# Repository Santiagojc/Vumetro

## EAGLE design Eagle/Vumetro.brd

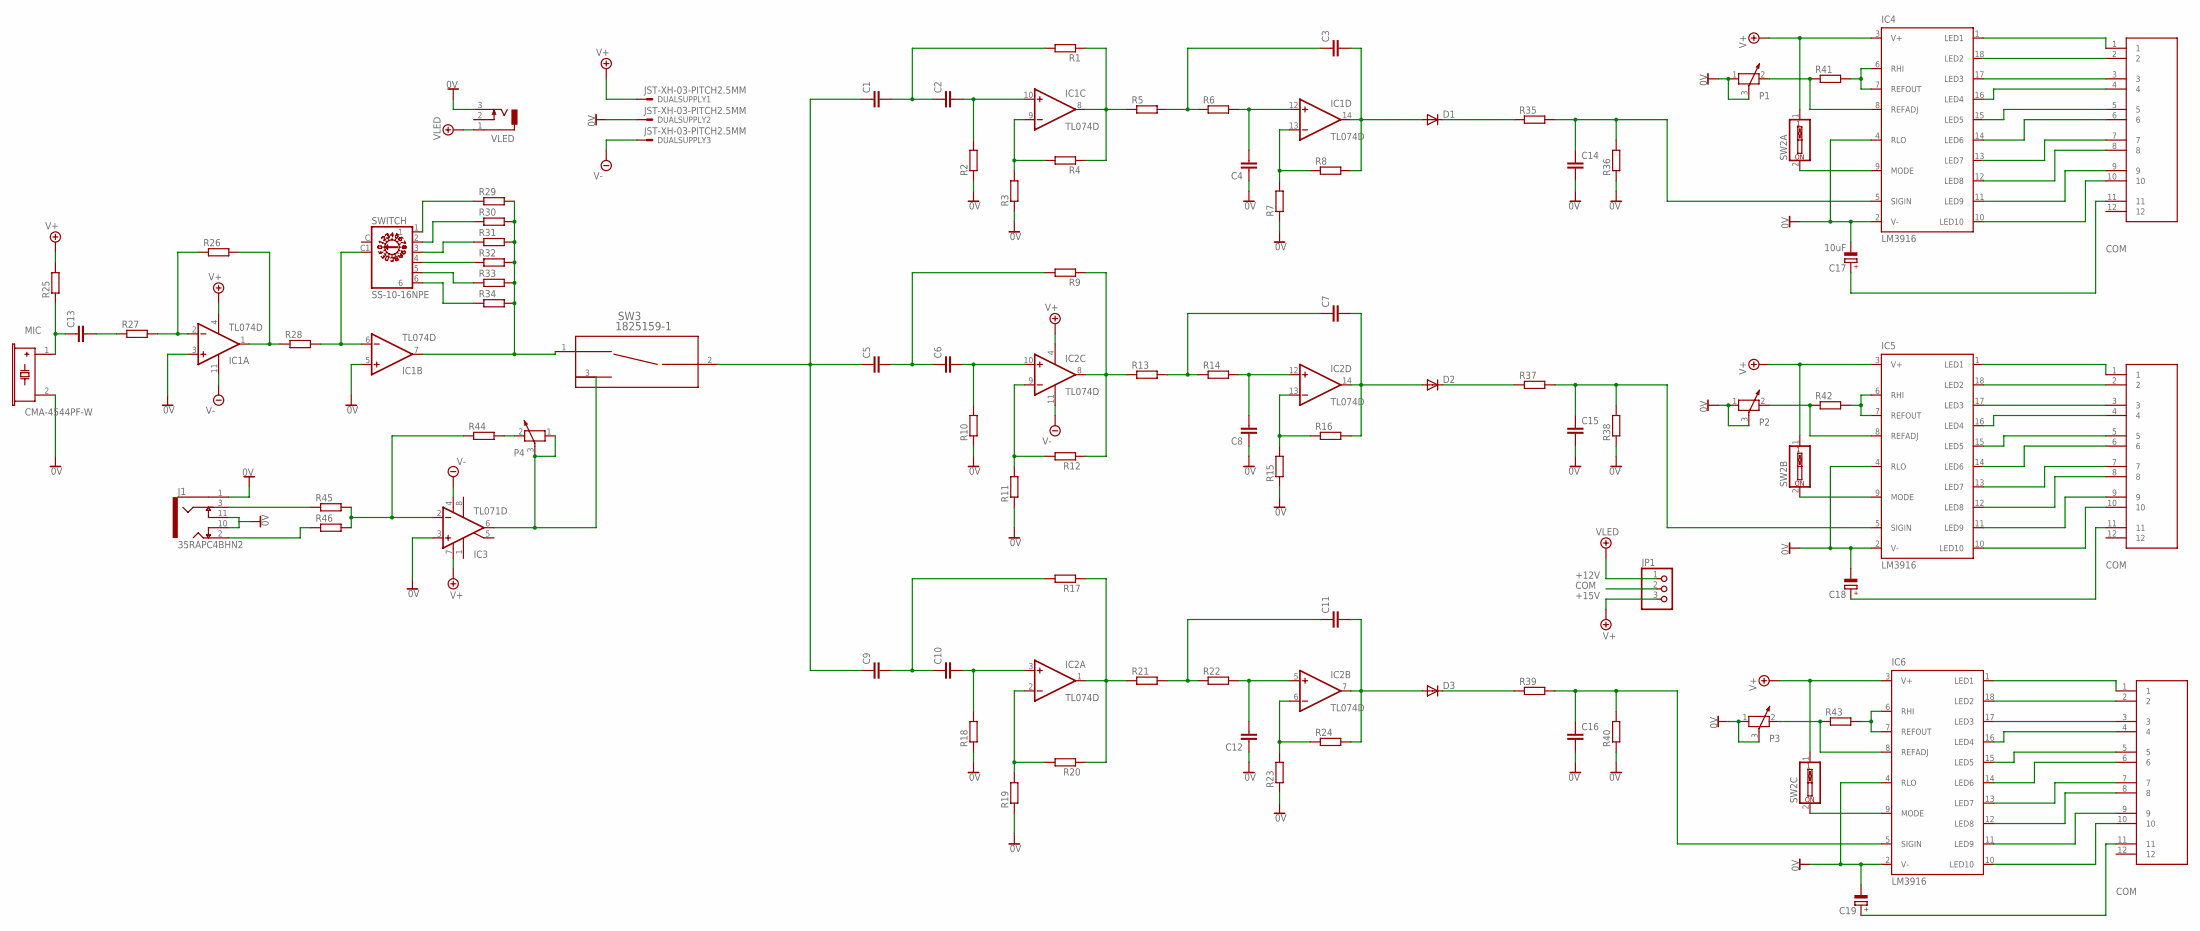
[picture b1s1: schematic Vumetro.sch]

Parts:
C1, C2, C3, C4, C5, C6, C7, C8, C9, C10, C11, C12, C13, C14, C15, C16: C-EUC2012; C2012
C17: 10uF; E2-4
C18, C19: CPOL-EUE2-4; E2-4
CON1, CON2, CON3: DF11-12DP-DIL; CON_12_2X6_DIL_DF11
D1, D2, D3: DIODE-SOD323-W; SOD323-W
DUALSUPPLY: JST-XH-03-PITCH2.5MM
IC1, IC2: TL074D; SO14
IC3: TL071D; SO08
IC4, IC5, IC6: LM3916; DIL18
J1: 35RAPC4BHN2; SWITCHCRAFT_35RAPC4BHN2
JP1: PINHD-1X3; 1X03
MIC: CMA-4544PF-W
P1, P2, P3, P4: POTENTIOMETER_P090; P090
R1, R2, R3, R4, R5, R6, R7, R8, R9, R10, R11, R12, R13, R14, R15, R16, R25, R26, R27, R28, R29, R30, R31, R32, R33, R34, R35, R36, R37, R38, R39, R40, R44, R45, R46: R-EU_R0805; R0805
R17, R18, R19, R20, R21, R22, R23, R24, R41, R42, R43: R-EU_M0805; M0805
SW2A, SW2B, SW2C: SW_DIP-1; EDG-01
SW3: 1825159-1; SW3-SLIDE-2POL_P98
SWITCH: SS-10-16NPE; P106
VLED: DCJ0303

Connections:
0V: C4.1, C8.1, C12.1, C14.2, C15.2, C16.2, C17.-, C18.-, C19.-, DUALSUPPLY.2, IC1.3 (+IN), IC1.5 (+IN), IC3.3 (+IN), IC4.2 (V-), IC4.4 (RLO), IC5.2 (V-), IC5.4 (RLO), IC6.2 (V-), IC6.4 (RLO), J1.1 (SLEEVE), J1.10 (TSH), J1.11 (RSH), MIC.2 (NEG), P1.1, P1.3, P2.1, P2.3, P3.1, P3.3, R2.1, R3.1, R7.1, R10.1, R11.1, R15.1, R18.1, R19.1, R23.1, R36.1, R38.1, R40.1, VLED.3
+12V: JP1.1, VLED.1
+15V: DUALSUPPLY.1, IC1.4 (V+), IC2.4 (V+), IC3.7 (V+), IC4.3 (V+), IC5.3 (V+), IC6.3 (V+), JP1.3, R25.2, SW2A.1, SW2B.1, SW2C.1
-15V: DUALSUPPLY.3, IC1.11 (V-), IC2.11 (V-), IC3.4 (V-)
COM: C17.+, C18.+, C19.+, CON1.11, CON2.11, CON3.11, JP1.2
unnamed: IC1.7 (OUT), R29.2, R30.2, R31.2, R32.2, R33.2, R34.2, SW3.1
unnamed: R29.1, SWITCH.1
unnamed: R30.1, SWITCH.2
unnamed: R31.1, SWITCH.3
unnamed: R32.1, SWITCH.4
unnamed: R33.1, SWITCH.5
unnamed: R34.1, SWITCH.6
unnamed: IC1.2 (-IN), R26.1, R27.2
unnamed: IC1.6 (-IN), R28.2, SWITCH.C1
unnamed: IC1.1 (OUT), R26.2, R28.1
unnamed: IC3.2 (-IN), R44.1, R45.2, R46.2
unnamed: P4.2, R44.2
unnamed: IC3.6 (OUT), P4.1, P4.3, SW3.3 (2)
unnamed: J1.3 (RING), R45.1
unnamed: J1.2 (TIP), R46.1
unnamed: C1.2, C2.1, R1.2
unnamed: C2.2, IC1.10 (+IN), R2.2
unnamed: IC1.9 (-IN), R3.2, R4.2
unnamed: IC1.8 (OUT), R1.1, R4.1, R5.1
unnamed: IC1.13 (-IN), R7.2, R8.1
unnamed: C3.2, D1.A, IC1.14 (OUT), R8.2
unnamed: C4.2, IC1.12 (+IN), R6.2
unnamed: C3.1, R5.2, R6.1
unnamed: C5.2, C6.1, R9.2
unnamed: C6.2, IC2.10 (+IN), R10.2
unnamed: IC2.9 (-IN), R11.2, R12.2
unnamed: IC2.8 (OUT), R9.1, R12.1, R13.1
unnamed: IC2.13 (-IN), R15.2, R16.1
unnamed: C7.2, D2.A, IC2.14 (OUT), R16.2
unnamed: C8.2, IC2.12 (+IN), R14.2
unnamed: C7.1, R13.2, R14.1
unnamed: C9.2, C10.1, R17.2
unnamed: C10.2, IC2.3 (+IN), R18.2
unnamed: IC2.2 (-IN), R19.2, R20.2
unnamed: IC2.1 (OUT), R17.1, R20.1, R21.1
unnamed: IC2.6 (-IN), R23.2, R24.1
unnamed: C11.2, D3.A, IC2.7 (OUT), R24.2
unnamed: C12.2, IC2.5 (+IN), R22.2
unnamed: C11.1, R21.2, R22.1
unnamed: C1.1, C5.1, C9.1, SW3.2 (3)
unnamed: D1.C, R35.1
unnamed: C14.1, IC4.5 (SIGIN), R35.2, R36.2
unnamed: D2.C, R37.1
unnamed: C15.1, IC5.5 (SIGIN), R37.2, R38.2
unnamed: D3.C, R39.1
unnamed: C16.1, IC6.5 (SIGIN), R39.2, R40.2
unnamed: C13.2, R27.1
unnamed: IC4.9 (MODE), SW2A.2
unnamed: IC4.6 (RHI), IC4.7 (REFOUT), R41.2
unnamed: IC4.8 (REFADJ), P1.2, R41.1
unnamed: C13.1, MIC.1 (POS), R25.1
unnamed: CON1.1, IC4.1 (LED1)
unnamed: CON1.2, IC4.18 (LED2)
unnamed: CON1.3, IC4.17 (LED3)
unnamed: CON1.4, IC4.16 (LED4)
unnamed: CON1.5, IC4.15 (LED5)
unnamed: CON1.6, IC4.14 (LED6)
unnamed: CON1.7, IC4.13 (LED7)
unnamed: CON1.8, IC4.12 (LED8)
unnamed: CON1.9, IC4.11 (LED9)
unnamed: CON1.10, IC4.10 (LED10)
unnamed: IC5.9 (MODE), SW2B.2
unnamed: IC5.6 (RHI), IC5.7 (REFOUT), R42.2
unnamed: IC5.8 (REFADJ), P2.2, R42.1
unnamed: CON2.1, IC5.1 (LED1)
unnamed: CON2.2, IC5.18 (LED2)
unnamed: CON2.3, IC5.17 (LED3)
unnamed: CON2.4, IC5.16 (LED4)
unnamed: CON2.5, IC5.15 (LED5)
unnamed: CON2.6, IC5.14 (LED6)
unnamed: CON2.7, IC5.13 (LED7)
unnamed: CON2.8, IC5.12 (LED8)
unnamed: CON2.9, IC5.11 (LED9)
unnamed: CON2.10, IC5.10 (LED10)
unnamed: IC6.9 (MODE), SW2C.2
unnamed: IC6.6 (RHI), IC6.7 (REFOUT), R43.2
unnamed: IC6.8 (REFADJ), P3.2, R43.1
unnamed: CON3.1, IC6.1 (LED1)
unnamed: CON3.2, IC6.18 (LED2)
unnamed: CON3.3, IC6.17 (LED3)
unnamed: CON3.4, IC6.16 (LED4)
unnamed: CON3.5, IC6.15 (LED5)
unnamed: CON3.6, IC6.14 (LED6)
unnamed: CON3.7, IC6.13 (LED7)
unnamed: CON3.8, IC6.12 (LED8)
unnamed: CON3.9, IC6.11 (LED9)
unnamed: CON3.10, IC6.10 (LED10)

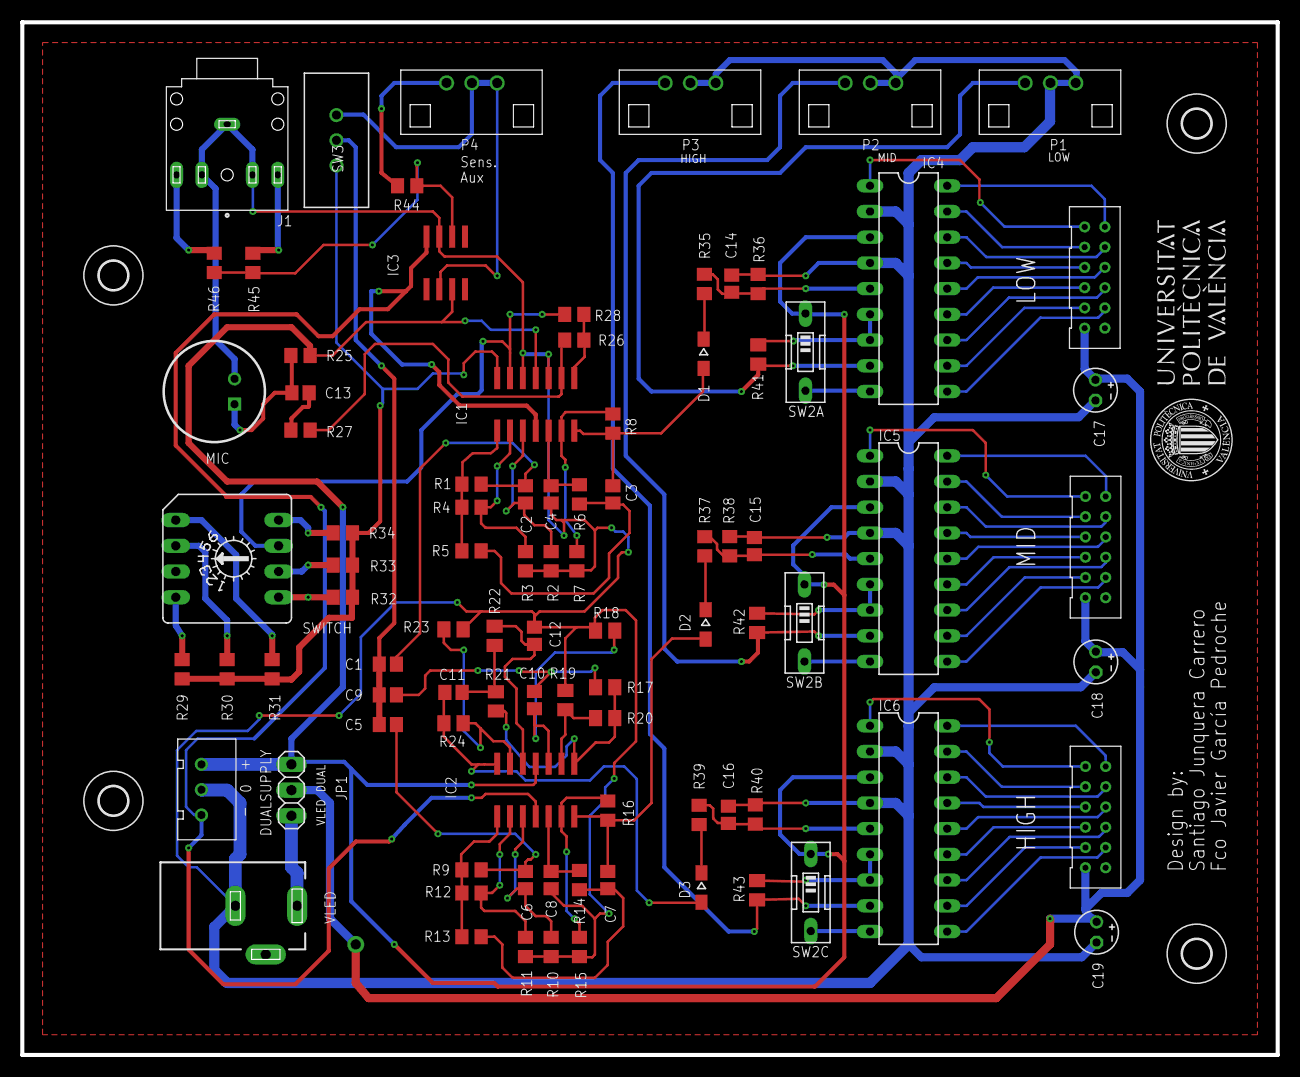
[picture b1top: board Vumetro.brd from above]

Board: 2 copper layers, 124.0 x 102.0 mm, 96 parts (0 on the bottom side), 92 nets.

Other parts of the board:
U$1: LOGOUPVTOP
U$4, U$5, U$6, U$7: 2,8

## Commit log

2018-06-04 Rename README.md to README.txt
